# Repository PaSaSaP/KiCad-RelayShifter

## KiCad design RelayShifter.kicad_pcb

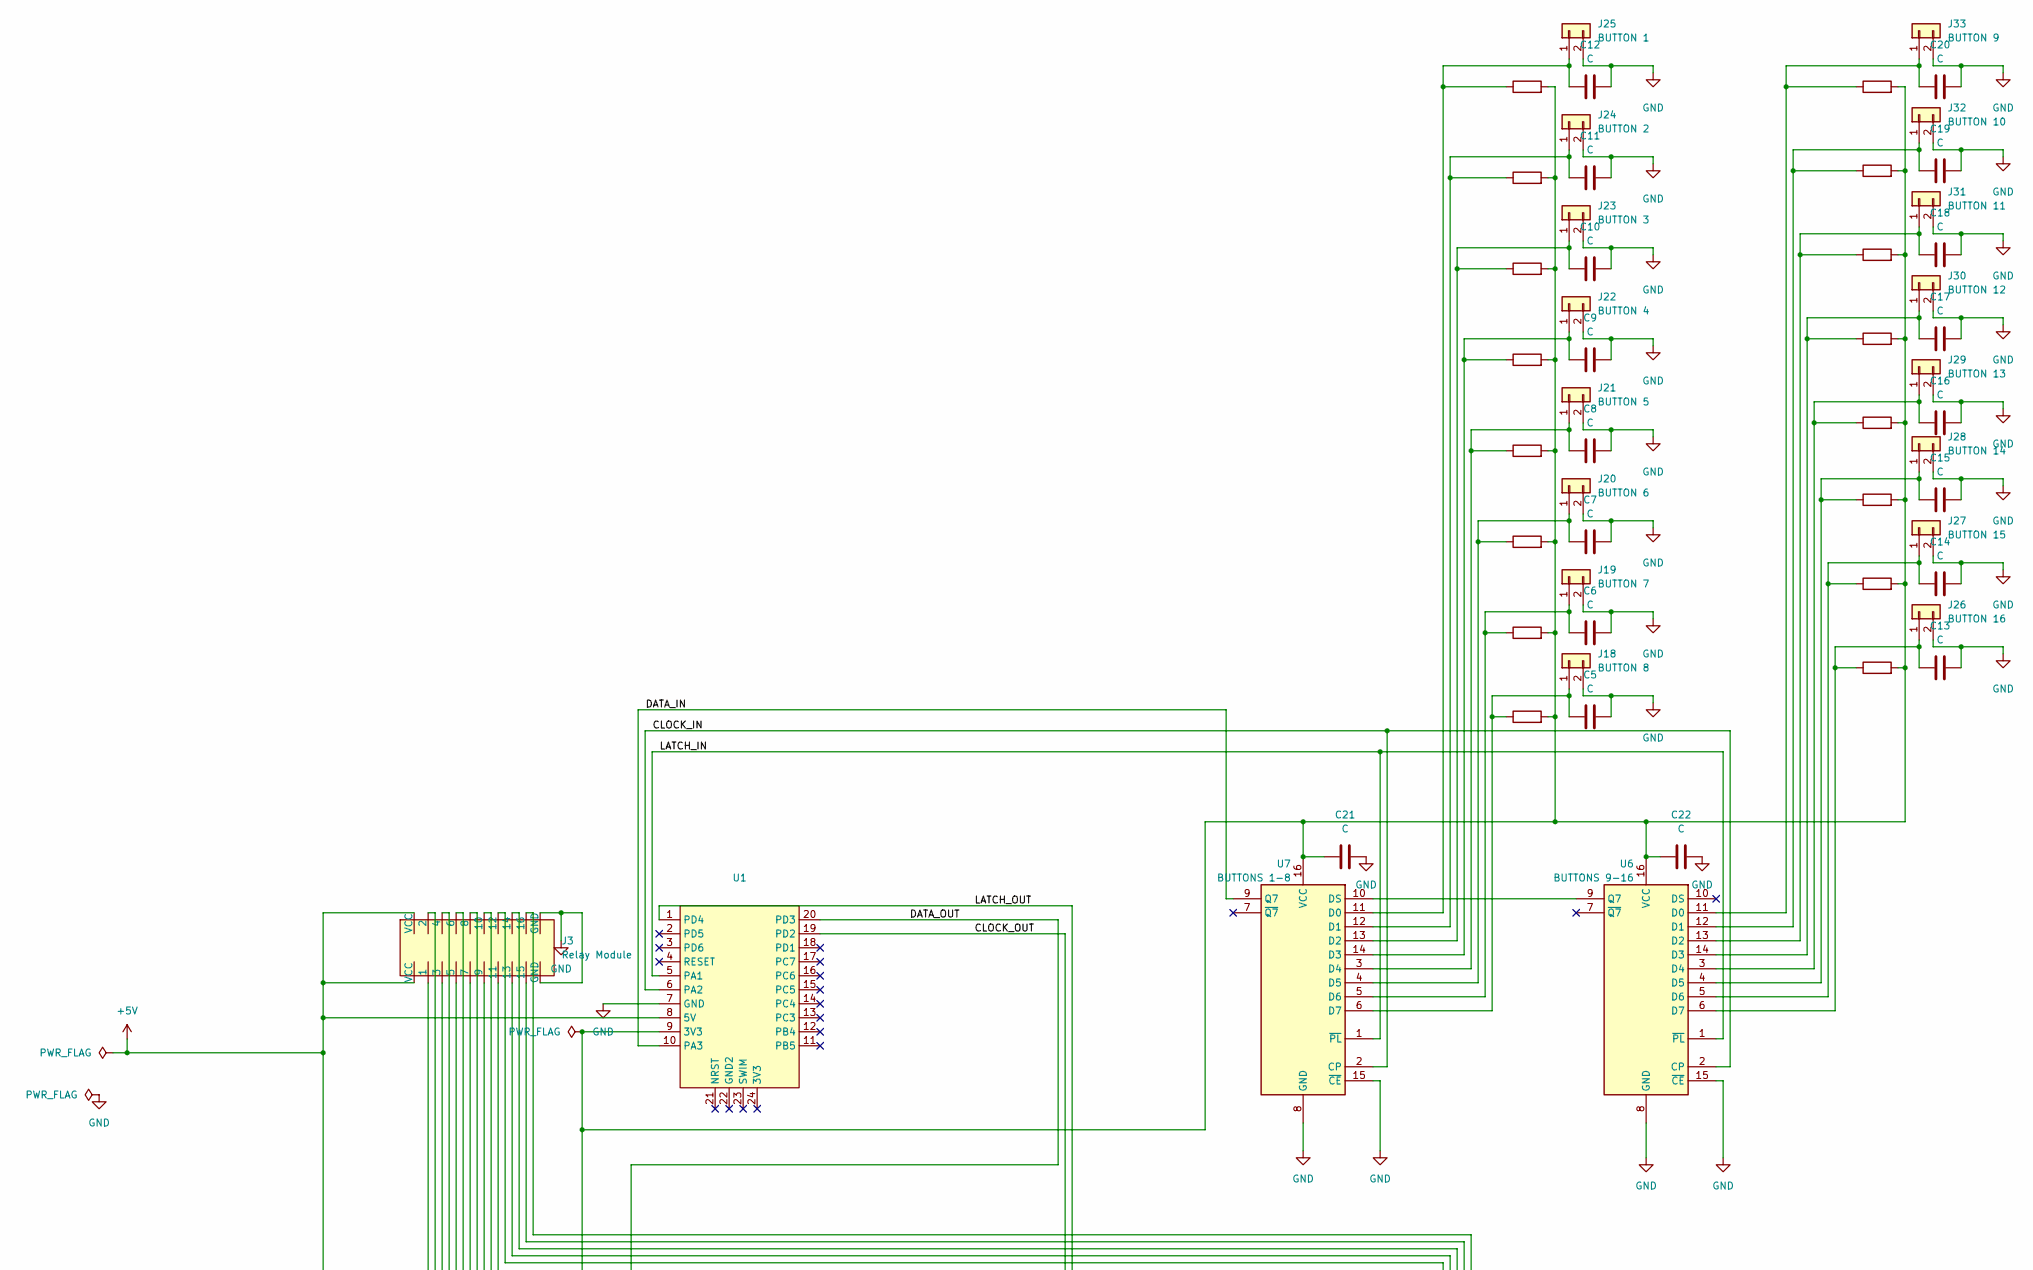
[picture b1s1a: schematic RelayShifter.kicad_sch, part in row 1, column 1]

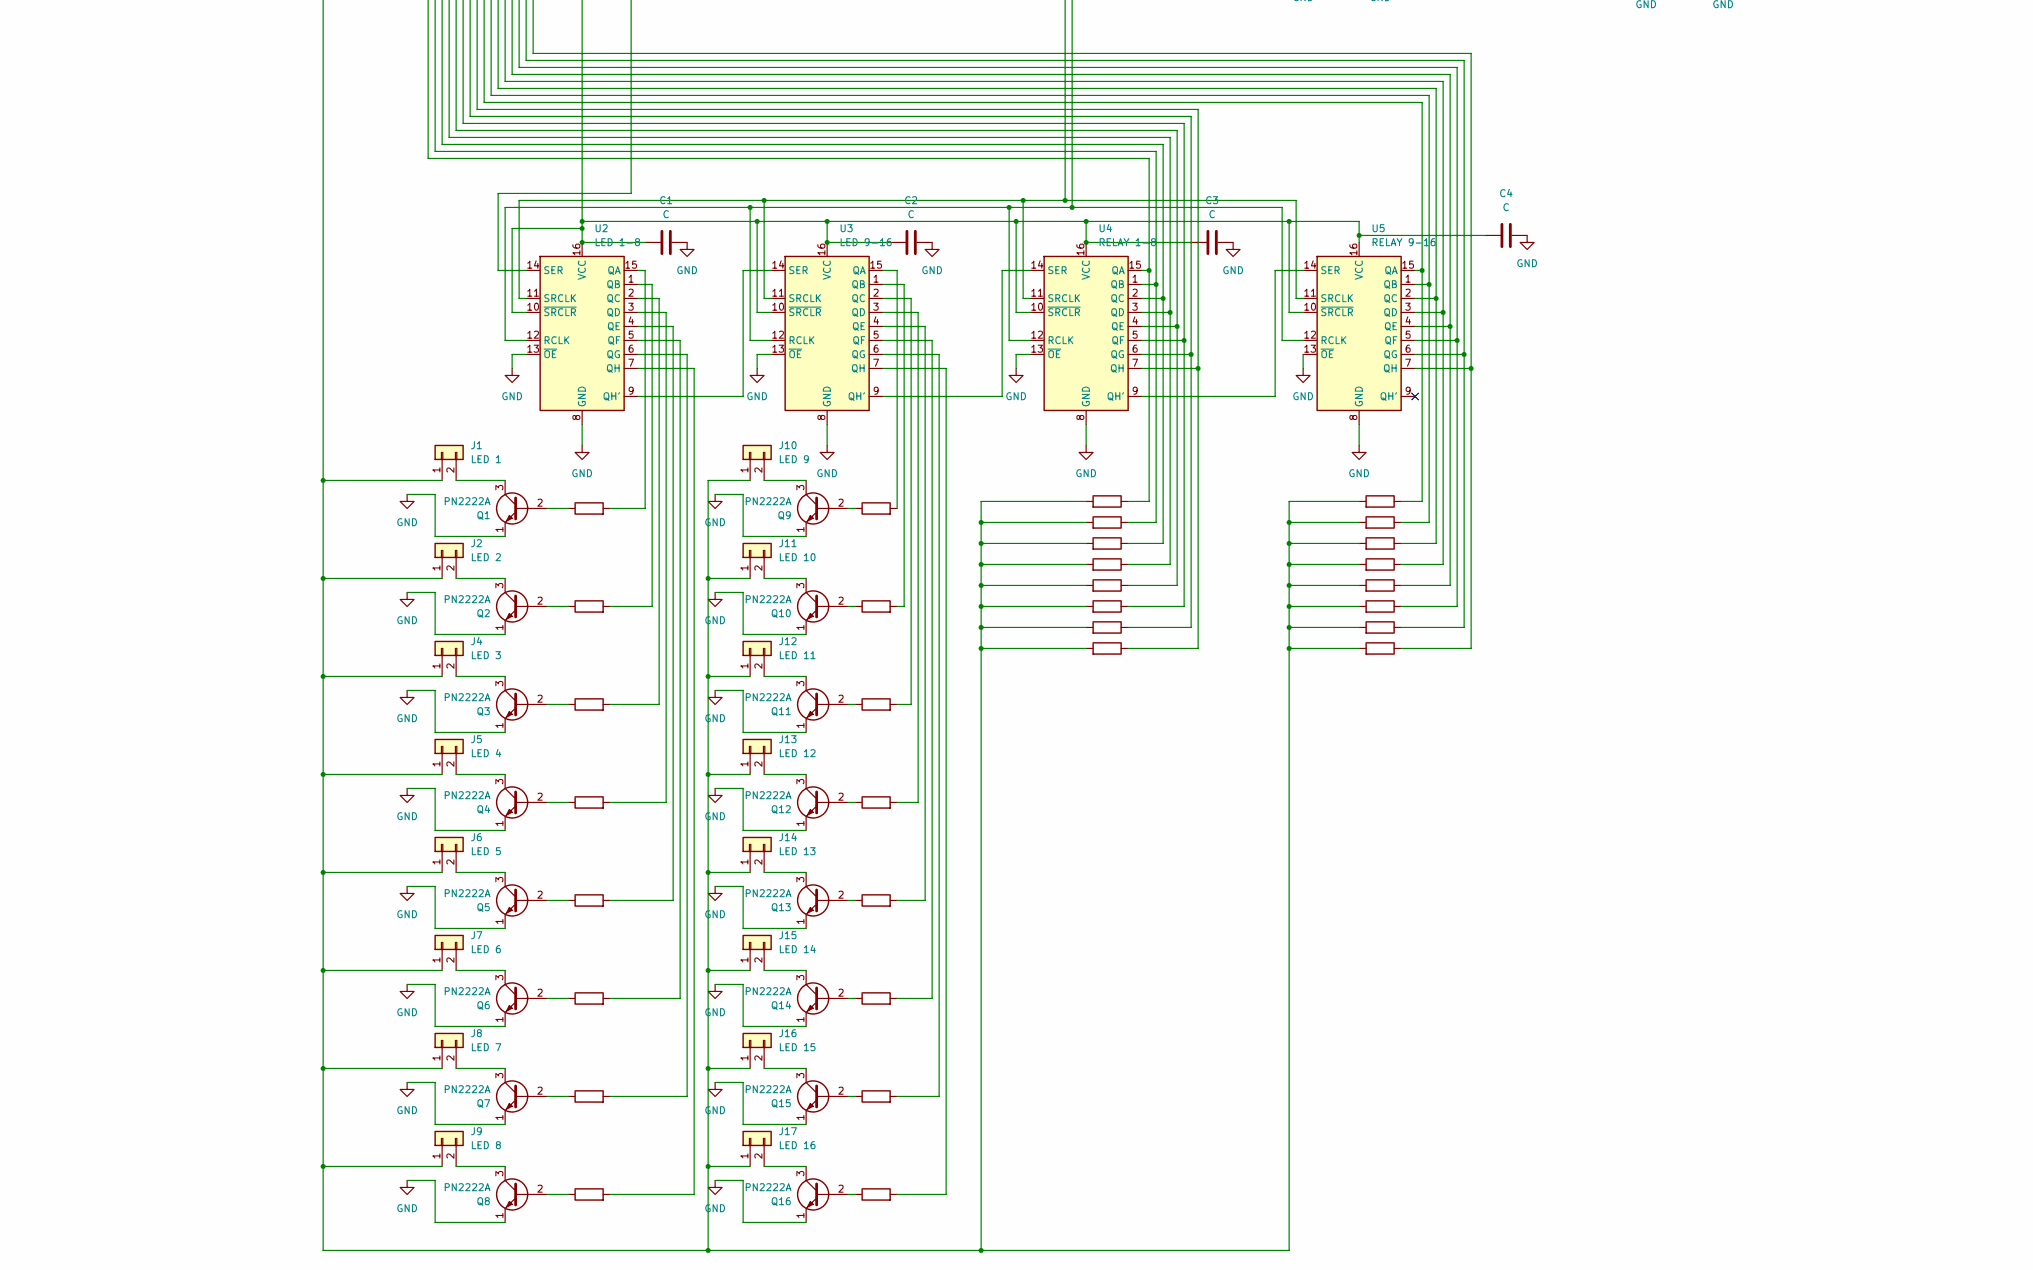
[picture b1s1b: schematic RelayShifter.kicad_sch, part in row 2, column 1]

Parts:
C1, C2, C3, C4, C5, C6, C7, C8, C9, C10, C11, C12, C13, C14, C15, C16, C17, C18, C19, C20, C21, C22: C; Conn_01x02 Small cap
J1: LED 1; Conn_01x02 Big Pads 5.08 Rotated
J2: LED 2; Conn_01x02 Big Pads 5.08 Rotated
J3: Relay Module; Conn_01x20 Big Pads Relay Module
J4: LED 3; Conn_01x02 Big Pads 5.08 Rotated
J5: LED 4; Conn_01x02 Big Pads 5.08 Rotated
J6: LED 5; Conn_01x02 Big Pads 5.08 Rotated
J7: LED 6; Conn_01x02 Big Pads 5.08 Rotated
J8: LED 7; Conn_01x02 Big Pads 5.08 Rotated
J9: LED 8; Conn_01x02 Big Pads 5.08 Rotated
J10: LED 9; Conn_01x02 Big Pads 5.08 Rotated
J11: LED 10; Conn_01x02 Big Pads 5.08 Rotated
J12: LED 11; Conn_01x02 Big Pads 5.08 Rotated
J13: LED 12; Conn_01x02 Big Pads 5.08 Rotated
J14: LED 13; Conn_01x02 Big Pads 5.08 Rotated
J15: LED 14; Conn_01x02 Big Pads 5.08 Rotated
J16: LED 15; Conn_01x02 Big Pads 5.08 Rotated
J17: LED 16; Conn_01x02 Big Pads 5.08 Rotated
J18: BUTTON 8; Conn_01x02 Big Pads 5.08 Rotated
J19: BUTTON 7; Conn_01x02 Big Pads 5.08 Rotated
J20: BUTTON 6; Conn_01x02 Big Pads 5.08 Rotated
J21: BUTTON 5; Conn_01x02 Big Pads 5.08 Rotated
J22: BUTTON 4; Conn_01x02 Big Pads 5.08 Rotated
J23: BUTTON 3; Conn_01x02 Big Pads 5.08 Rotated
J24: BUTTON 2; Conn_01x02 Big Pads 5.08 Rotated
J25: BUTTON 1; Conn_01x02 Big Pads 5.08 Rotated
J26: BUTTON 16; Conn_01x02 Big Pads 5.08 Rotated
J27: BUTTON 15; Conn_01x02 Big Pads 5.08 Rotated
J28: BUTTON 14; Conn_01x02 Big Pads 5.08 Rotated
J29: BUTTON 13; Conn_01x02 Big Pads 5.08 Rotated
J30: BUTTON 12; Conn_01x02 Big Pads 5.08 Rotated
J31: BUTTON 11; Conn_01x02 Big Pads 5.08 Rotated
J32: BUTTON 10; Conn_01x02 Big Pads 5.08 Rotated
J33: BUTTON 9; Conn_01x02 Big Pads 5.08 Rotated
Q1, Q2, Q3, Q4, Q5, Q6, Q7, Q8, Q9, Q10, Q11, Q12, Q13, Q14, Q15, Q16: PN2222A; Conn_01x03 small T 2-1-3 B-E-C BEC
R1, R2, R3, R4, R5, R6, R7, R8, R9, R10, R11, R12, R13, R14, R15, R16: 4k7; Conn_01x02 7.62 Resistor Vertically
R17, R18, R19, R20, R21, R22, R23, R24, R25, R26, R27, R28, R29, R30, R31, R32, R33, R34, R35, R36, R37, R38, R39, R40, R41, R42, R43, R44, R45, R46, R47, R48: 68K; Conn_01x02 7.62 Resistor Vertically
U1: STM8S BLUE No Prog Pads
U2: LED 1-8; DIP-16_W7.62mm shift register HC Big Pads
U3: LED 9-16; DIP-16_W7.62mm shift register HC Big Pads
U4: RELAY 1-8; DIP-16_W7.62mm shift register HC Big Pads
U5: RELAY 9-16; DIP-16_W7.62mm shift register HC Big Pads
U6: BUTTONS 9-16; DIP-16_W7.62mm shift register HC Big Pads
U7: BUTTONS 1-8; DIP-16_W7.62mm shift register HC Big Pads

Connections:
+5V: J1.1, J2.1, J3.17 (VCC), J3.18 (VCC), J4.1, J5.1, J6.1, J7.1, J8.1, J9.1, J10.1, J11.1, J12.1, J13.1, J14.1, J15.1, J16.1, J17.1, R17.2, R18.2, R19.2, R20.2, R21.2, R22.2, R23.2, R24.2, R25.2, R26.2, R27.2, R28.2, R29.2, R30.2, R31.2, R32.2, U1.8 (5V)
/CLOCK_IN: U1.6 (PA2), U6.2 (CP), U7.2 (CP)
/CLOCK_OUT: U1.19 (PD2), U2.11 (SRCLK), U3.11 (SRCLK), U4.11 (SRCLK), U5.11 (SRCLK)
/DATA_IN: U1.10 (PA3), U7.9 (Q7)
/DATA_OUT: U1.20 (PD3), U2.14 (SER)
/LATCH_IN: U1.5 (PA1), U6.1 (~PL), U7.1 (~PL)
/LATCH_OUT: U1.1 (PD4), U2.12 (RCLK), U3.12 (RCLK), U4.12 (RCLK), U5.12 (RCLK)
GND: C1.2, C2.2, C3.2, C4.2, C5.2, C6.2, C7.2, C8.2, C9.2, C10.2, C11.2, C12.2, C13.2, C14.2, C15.2, C16.2, C17.2, C18.2, C19.2, C20.2, C21.2, C22.2, J3.19 (GND), J3.20 (GND), J18.2, J19.2, J20.2, J21.2, J22.2, J23.2, J24.2, J25.2, J26.2, J27.2, J28.2, J29.2, J30.2, J31.2, J32.2, J33.2, Q1.1 (E), Q2.1 (E), Q3.1 (E), Q4.1 (E), Q5.1 (E), Q6.1 (E), Q7.1 (E), Q8.1 (E), Q9.1 (E), Q10.1 (E), Q11.1 (E), Q12.1 (E), Q13.1 (E), Q14.1 (E), Q15.1 (E), Q16.1 (E), U1.7 (GND), U2.8 (GND), U2.13 (~OE), U3.8 (GND), U3.13 (~OE), U4.8 (GND), U4.13 (~OE), U5.8 (GND), U5.13 (~OE), U6.8 (GND), U6.15 (~CE), U7.8 (GND), U7.15 (~CE)
unnamed: J1.2, Q1.3 (C)
unnamed: J2.2, Q2.3 (C)
unnamed: J4.2, Q3.3 (C)
unnamed: J5.2, Q4.3 (C)
unnamed: J6.2, Q5.3 (C)
unnamed: J7.2, Q6.3 (C)
unnamed: J8.2, Q7.3 (C)
unnamed: J9.2, Q8.3 (C)
unnamed: J10.2, Q9.3 (C)
unnamed: J11.2, Q10.3 (C)
unnamed: J12.2, Q11.3 (C)
unnamed: J13.2, Q12.3 (C)
unnamed: J14.2, Q13.3 (C)
unnamed: J15.2, Q14.3 (C)
unnamed: J16.2, Q15.3 (C)
unnamed: J17.2, Q16.3 (C)
unnamed: C5.1, J18.1, R33.1, U7.6 (D7)
unnamed: C6.1, J19.1, R34.1, U7.5 (D6)
unnamed: C7.1, J20.1, R35.1, U7.4 (D5)
unnamed: C8.1, J21.1, R36.1, U7.3 (D4)
unnamed: C9.1, J22.1, R37.1, U7.14 (D3)
unnamed: C10.1, J23.1, R38.1, U7.13 (D2)
unnamed: C11.1, J24.1, R39.1, U7.12 (D1)
unnamed: C12.1, J25.1, R40.1, U7.11 (D0)
unnamed: C13.1, J26.1, R41.1, U6.6 (D7)
unnamed: C14.1, J27.1, R42.1, U6.5 (D6)
unnamed: C15.1, J28.1, R43.1, U6.4 (D5)
unnamed: C16.1, J29.1, R44.1, U6.3 (D4)
unnamed: C17.1, J30.1, R45.1, U6.14 (D3)
unnamed: C18.1, J31.1, R46.1, U6.13 (D2)
unnamed: C19.1, J32.1, R47.1, U6.12 (D1)
unnamed: C20.1, J33.1, R48.1, U6.11 (D0)
unnamed: Q1.2 (B), R1.1
unnamed: Q2.2 (B), R2.1
unnamed: Q3.2 (B), R3.1
unnamed: Q4.2 (B), R4.1
unnamed: Q5.2 (B), R5.1
unnamed: Q6.2 (B), R6.1
unnamed: Q7.2 (B), R7.1
unnamed: Q8.2 (B), R8.1
unnamed: Q9.2 (B), R9.1
unnamed: Q10.2 (B), R10.1
unnamed: Q11.2 (B), R11.1
unnamed: Q12.2 (B), R12.1
unnamed: Q13.2 (B), R13.1
unnamed: Q14.2 (B), R14.1
unnamed: Q15.2 (B), R15.1
unnamed: Q16.2 (B), R16.1
unnamed: R1.2, U2.15 (QA)
unnamed: R2.2, U2.1 (QB)
unnamed: R3.2, U2.2 (QC)
unnamed: R4.2, U2.3 (QD)
unnamed: R5.2, U2.4 (QE)
unnamed: R6.2, U2.5 (QF)
unnamed: R7.2, U2.6 (QG)
unnamed: U2.9 (QH'), U3.14 (SER)
unnamed: R8.2, U2.7 (QH)
unnamed: C1.1, C2.1, C3.1, C4.1, C21.1, C22.1, R33.2, R34.2, R35.2, R36.2, R37.2, R38.2, R39.2, R40.2, R41.2, R42.2, R43.2, R44.2, R45.2, R46.2, R47.2, R48.2, U1.9 (3V3), U2.10 (~SRCLR), U2.16 (VCC), U3.10 (~SRCLR), U3.16 (VCC), U4.10 (~SRCLR), U4.16 (VCC), U5.10 (~SRCLR), U5.16 (VCC), U6.16 (VCC), U7.16 (VCC)
unnamed: R9.2, U3.15 (QA)
unnamed: R10.2, U3.1 (QB)
unnamed: R11.2, U3.2 (QC)
unnamed: R12.2, U3.3 (QD)
unnamed: R13.2, U3.4 (QE)
unnamed: R14.2, U3.5 (QF)
unnamed: R15.2, U3.6 (QG)
unnamed: U3.9 (QH'), U4.14 (SER)
unnamed: R16.2, U3.7 (QH)
unnamed: J3.1, R17.1, U4.15 (QA)
unnamed: J3.2, R18.1, U4.1 (QB)
unnamed: J3.3, R19.1, U4.2 (QC)
unnamed: J3.4, R20.1, U4.3 (QD)
unnamed: J3.5, R21.1, U4.4 (QE)
unnamed: J3.6, R22.1, U4.5 (QF)
unnamed: J3.7, R23.1, U4.6 (QG)
unnamed: U4.9 (QH'), U5.14 (SER)
unnamed: J3.8, R24.1, U4.7 (QH)
unnamed: J3.9, R25.1, U5.15 (QA)
unnamed: J3.10, R26.1, U5.1 (QB)
unnamed: J3.11, R27.1, U5.2 (QC)
unnamed: J3.12, R28.1, U5.3 (QD)
unnamed: J3.13, R29.1, U5.4 (QE)
unnamed: J3.14, R30.1, U5.5 (QF)
unnamed: J3.15, R31.1, U5.6 (QG)
unnamed: J3.16, R32.1, U5.7 (QH)
unnamed: U6.9 (Q7), U7.10 (DS)

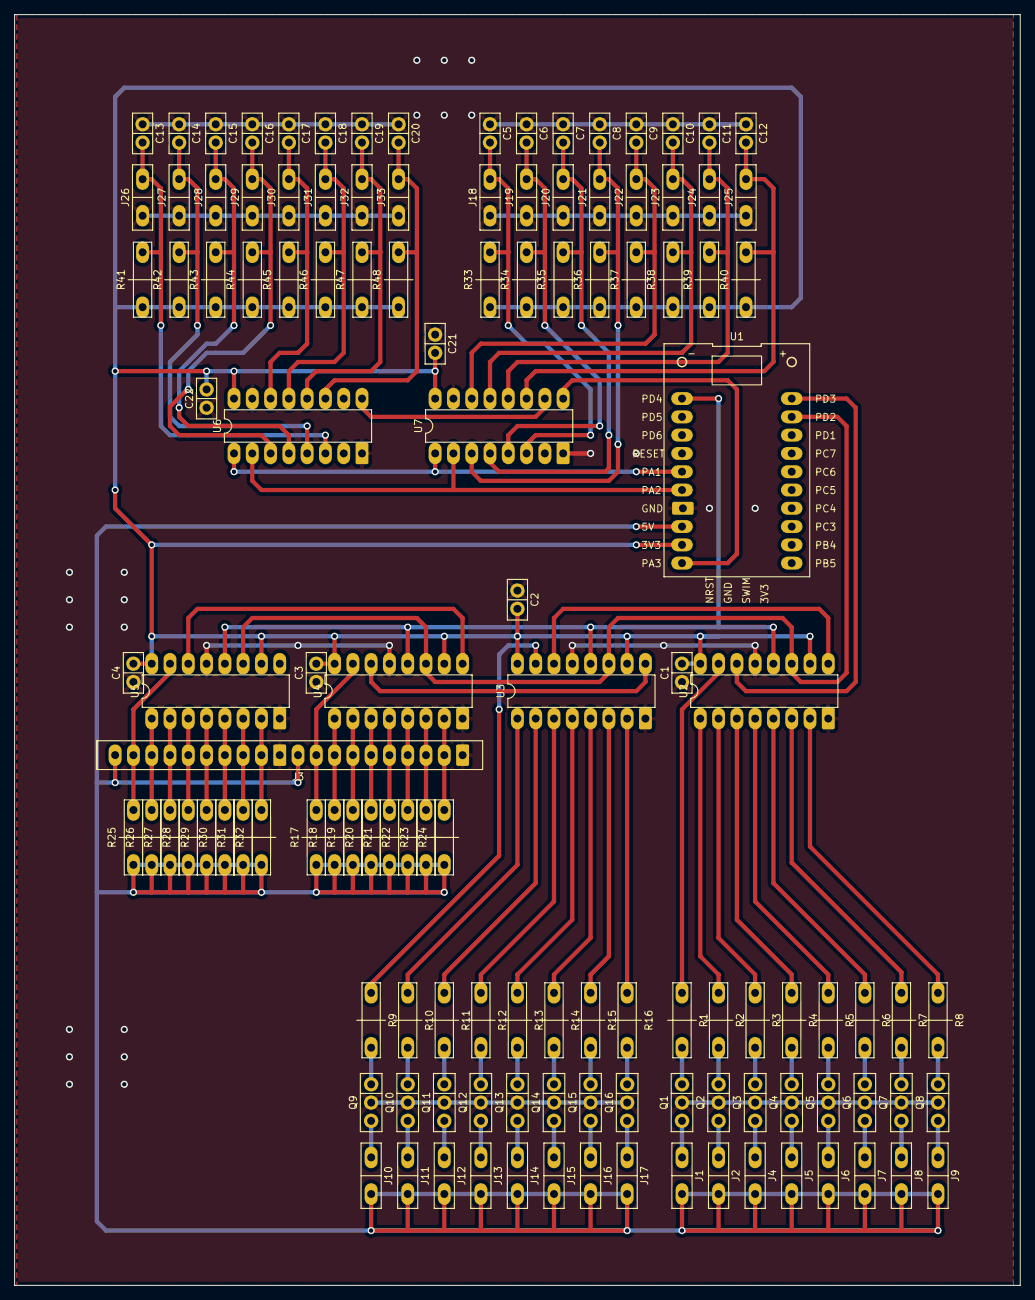
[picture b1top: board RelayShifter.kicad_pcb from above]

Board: 2 copper layers, 139.7 x 176.5 mm, 126 parts (0 on the bottom side), 93 nets.

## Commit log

2026-02-06 Relay Shifter v1
